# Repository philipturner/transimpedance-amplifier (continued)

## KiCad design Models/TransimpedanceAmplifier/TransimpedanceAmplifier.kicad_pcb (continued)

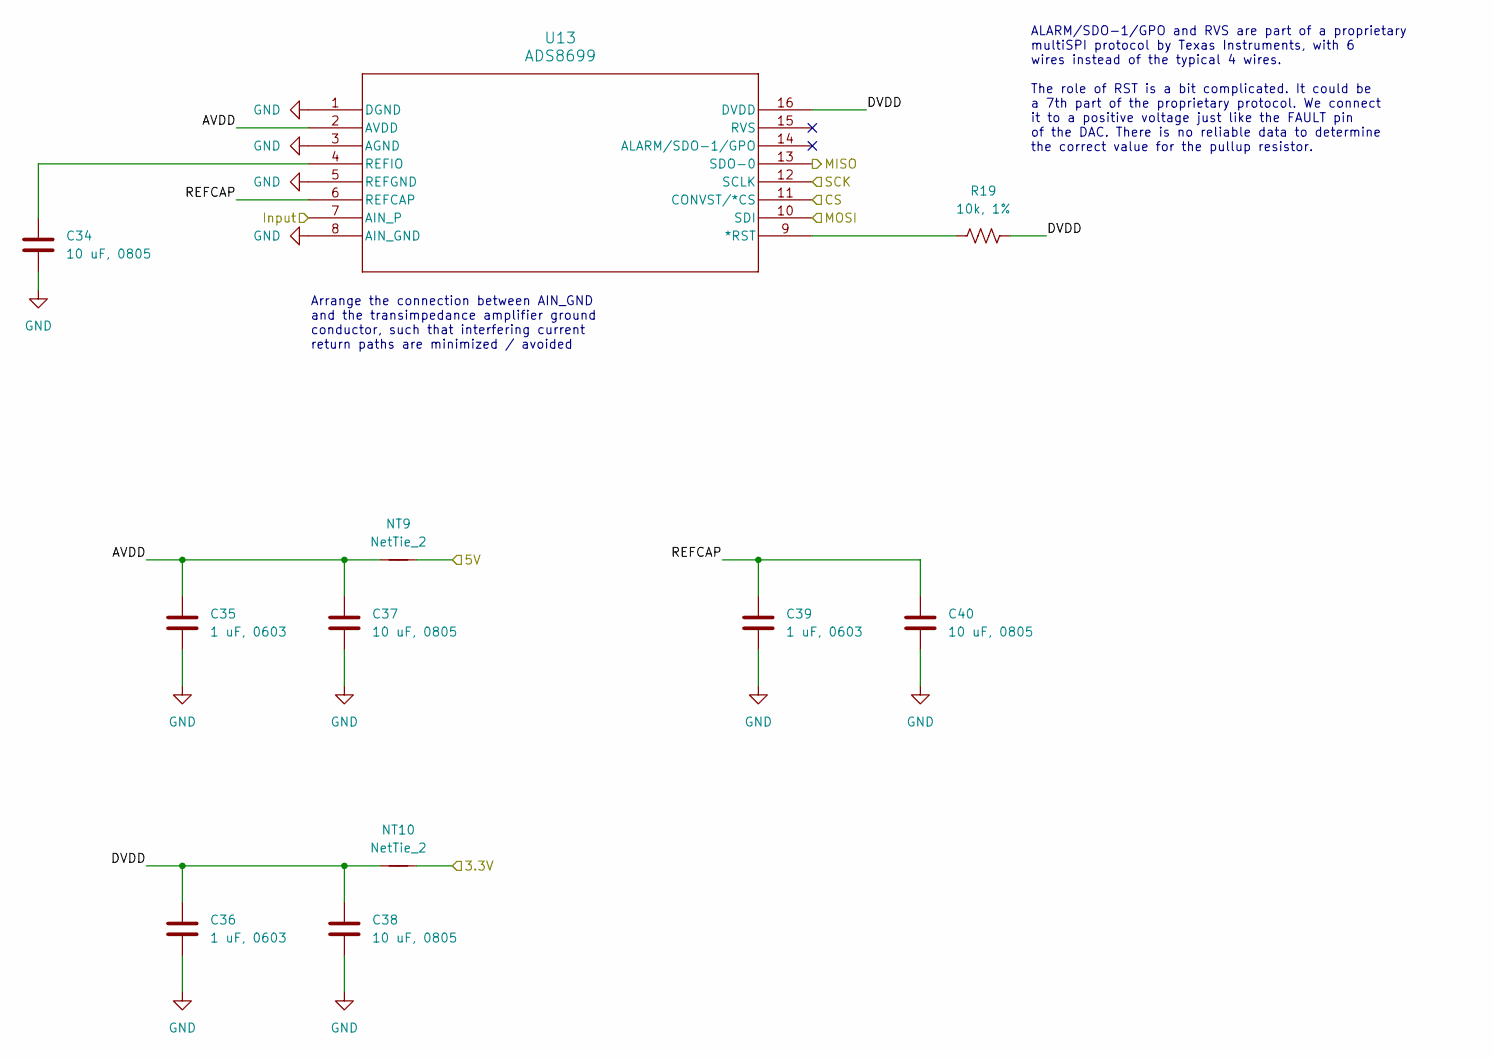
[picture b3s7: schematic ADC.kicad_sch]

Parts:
C34, C37, C38, C40: 10 uF, 0805; CAPC0805
C35, C36, C39: 1 uF, 0603; CAPC0603
NT9, NT10: NetTie_2; NetTie_0.2mm
R19: 10k, 1%; RESC0603
U13: ADS8699

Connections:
/3.3V_Converter: NT10.2; also elsewhere on the board
/5V_Converter: NT9.2; also elsewhere on the board
/CPU/ADC/AVDD: C35.1, C37.1, NT9.1, U13.2 (AVDD)
/CPU/ADC/CS: U13.11 (CONVST/*CS); also elsewhere on the board
/CPU/ADC/DVDD: C36.1, C38.1, NT10.1, R19.2, U13.16 (DVDD)
/CPU/ADC/MISO: U13.13 (SDO-0); also elsewhere on the board
/CPU/ADC/MOSI: U13.10 (SDI); also elsewhere on the board
/CPU/ADC/REFCAP: C39.1, C40.1, U13.6 (REFCAP)
/CPU/ADC/SCK: U13.12 (SCLK); also elsewhere on the board
/CPU/ADC_Input: U13.7 (AIN_P); also elsewhere on the board
GND: C34.2, C35.2, C36.2, C37.2, C38.2, C39.2, C40.2, U13.1 (DGND), U13.3 (AGND), U13.5 (REFGND), U13.8 (AIN_GND); also elsewhere on the board
unnamed: R19.1, U13.9 (*RST)
unnamed: C34.1, U13.4 (REFIO)

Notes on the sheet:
ALARM/SDO-1/GPO and RVS are part of a proprietary multiSPI protocol by Texas Instruments, with 6 wires instead of the typical 4 wires. The role of RST is a bit complicated. It could be a 7th part of the proprietary protocol. We connect it to a positive voltage just like the FAULT pin of the DAC. Th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
Arrange the connection between AIN_GND and the transimpedance amplifier ground conductor, such that interfering current return paths are minimized / avoided

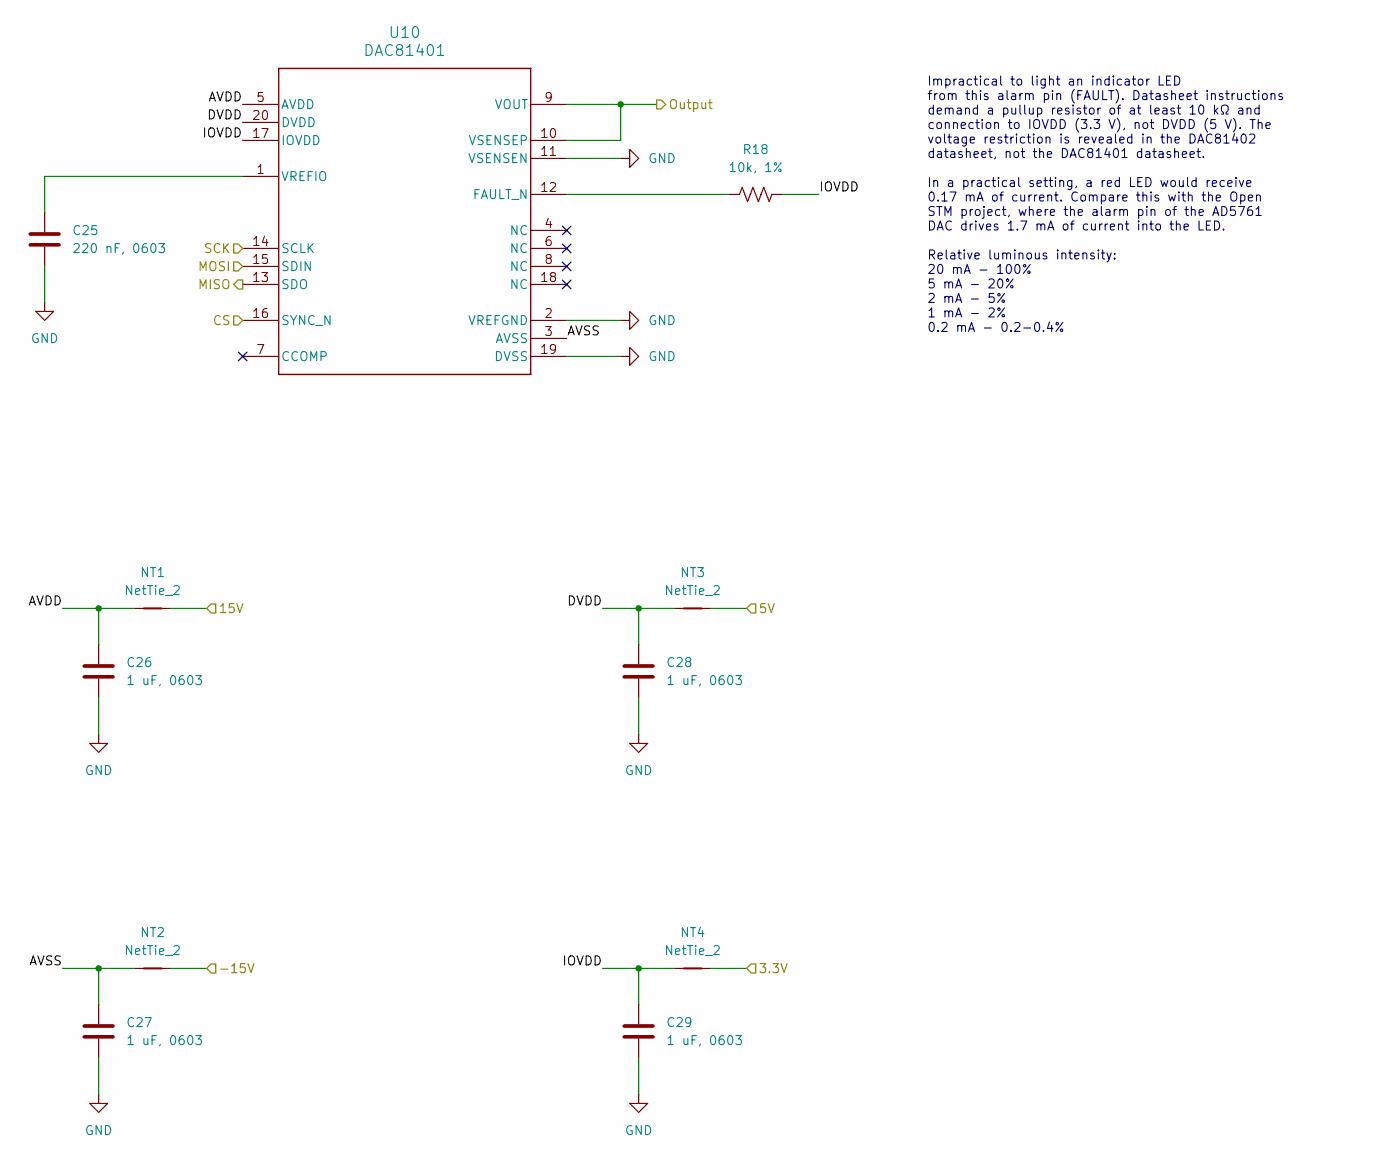
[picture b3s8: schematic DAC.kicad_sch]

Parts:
C25: 220 nF, 0603; CAPC0603
C26, C27, C28, C29: 1 uF, 0603; CAPC0603
NT1, NT2, NT3, NT4: NetTie_2; NetTie_0.2mm
R18: 10k, 1%; RESC0603
U10: DAC81401

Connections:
/3.3V_Converter: NT4.2; also elsewhere on the board
/5V_Converter: NT3.2; also elsewhere on the board
/15V: NT1.2; also elsewhere on the board
/-15V: NT2.2; also elsewhere on the board
/CPU/DAC/AVDD: C26.1, NT1.1, U10.5 (AVDD)
/CPU/DAC/AVSS: C27.1, NT2.1, U10.3 (AVSS)
/CPU/DAC/CS: U10.16 (SYNC_N); also elsewhere on the board
/CPU/DAC/DVDD: C28.1, NT3.1, U10.20 (DVDD)
/CPU/DAC/IOVDD: C29.1, NT4.1, R18.2, U10.17 (IOVDD)
/CPU/DAC/MISO: U10.13 (SDO); also elsewhere on the board
/CPU/DAC/MOSI: U10.15 (SDIN); also elsewhere on the board
/CPU/DAC/SCK: U10.14 (SCLK); also elsewhere on the board
/CPU/DAC_Output: U10.9 (VOUT), U10.10 (VSENSEP); also elsewhere on the board
GND: C25.2, C26.2, C27.2, C28.2, C29.2, U10.2 (VREFGND), U10.11 (VSENSEN), U10.19 (DVSS); also elsewhere on the board
unnamed: R18.1, U10.12 (FAULT_N)
unnamed: C25.1, U10.1 (VREFIO)

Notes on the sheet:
Impractical to light an indicator LED from this alarm pin (FAULT). Datasheet instructions demand a pullup resistor of at least 10 kΩ and connection to IOVDD (3.3 V), not DVDD (5 V). The voltage restriction is revealed in the DAC81402 datasheet, not the DAC81401 datasheet. In a practical setting, a 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

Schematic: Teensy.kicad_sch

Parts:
J11, J14: Conn_01x24_Socket; PinSocket_1x24
J12, J13: Conn_01x24_Pin
U14: Teensy4.1

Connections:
/CPU/Isolation/3.3V_Digital: J11.15, J14.22; also elsewhere on the board
/CPU/Isolation/CS_ADC_Digital: J14.5; also elsewhere on the board
/CPU/Isolation/CS_DAC_Digital: J14.4; also elsewhere on the board
/CPU/Isolation/GND_Digital: J11.1, J14.10, J14.23; also elsewhere on the board
/CPU/Isolation/MISO_Digital: J11.14; also elsewhere on the board
/CPU/Isolation/MOSI_Digital: J11.13; also elsewhere on the board
/CPU/Isolation/SCK_Digital: J14.11; also elsewhere on the board
unnamed: J12.1, U14.1 (GND)
unnamed: J12.2, U14.2 (0_RX1_CRX2_CS1)
unnamed: J12.3, U14.3 (1_TX1_CTX2_MISO1)
unnamed: J12.4, U14.4 (2_OUT2)
unnamed: J12.5, U14.5 (3_LRCLK2)
unnamed: J12.6, U14.6 (4_BCLK2)
unnamed: J12.7, U14.7 (5_IN2)
unnamed: J12.8, U14.8 (6_OUT1D)
unnamed: J12.9, U14.9 (7_RX2_OUT1A)
unnamed: J12.10, U14.10 (8_TX2_IN1)
unnamed: J12.11, U14.11 (9_OUT1C)
unnamed: J12.12, U14.12 (10_CS_MQSR)
unnamed: J12.13, U14.13 (11_MOSI_CTX1)
unnamed: J12.14, U14.14 (12_MISO_MQSL)
unnamed: J12.15, U14.15 (3V3)
unnamed: J12.16, U14.16 (24_A10_TX6_SCL2)
unnamed: J12.17, U14.17 (25_A11_RX6_SDA2)
unnamed: J12.18, U14.18 (26_A12_MOSI1)
unnamed: J12.19, U14.19 (27_A13_SCK1)
unnamed: J12.20, U14.20 (28_RX7)
unnamed: J12.21, U14.21 (29_TX7)
unnamed: J12.22, U14.22 (30_CRX3)
unnamed: J12.23, U14.23 (31_CTX3)
unnamed: J12.24, U14.24 (32_OUT1B)
unnamed: J13.1, U14.25 (33_MCLK2)
unnamed: J13.2, U14.26 (34_RX8)
unnamed: J13.3, U14.27 (35_TX8)
unnamed: J13.4, U14.28 (36_CS)
unnamed: J13.5, U14.29 (37_CS)
unnamed: J13.6, U14.30 (38_CS1_IN1)
unnamed: J13.7, U14.31 (39_MISO1_OUT1A)
unnamed: J13.8, U14.32 (40_A16)
unnamed: J13.9, U14.33 (41_A17)
unnamed: J13.10, U14.34 (GND)
unnamed: J13.11, U14.35 (13_SCK_LED)
unnamed: J13.12, U14.36 (14_A0_TX3_SPDIF_OUT)
unnamed: J13.13, U14.37 (15_A1_RX3_SPDIF_IN)
unnamed: J13.14, U14.38 (16_A2_RX4_SCL1)
unnamed: J13.15, U14.39 (17_A3_TX4_SDA1)
unnamed: J13.16, U14.40 (18_A4_SDA)
unnamed: J13.17, U14.41 (19_A5_SCL)
unnamed: J13.18, U14.42 (20_A6_TX5_LRCLK1)
unnamed: J13.19, U14.43 (21_A7_RX5_BCLK1)
unnamed: J13.20, U14.44 (22_A8_CTX1)
unnamed: J13.21, U14.45 (23_A9_CRX1_MCLK1)
unnamed: J13.22, U14.46 (3V3)
unnamed: J13.23, U14.47 (GND)
unnamed: J13.24, U14.48 (VIN)

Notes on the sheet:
Connected to low-cost Windows PC through Micro-USB port: 49 (VUSB) 66 (D-) 67 (D+) GND
All 3.3V pins are electrically equivalent. They connect to the same net in the Teensy 4.1 PCB schematic. In theory, I can draw 250 mA out of any one of them. Their physical separation is mostly an issue at high frequencies, where local decoupling networks are used anyway. The same should be true ab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

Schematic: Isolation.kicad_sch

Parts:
C30, C31, C32, C33: 100 nF, 0603; CAPC0603
NT5, NT6, NT7, NT8: NetTie_2; NetTie_0.2mm
U11, U12: ISO7641FM

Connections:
/3.3V_Converter: NT7.2, NT8.2, U11.10 (EN2), U12.10 (EN2); also elsewhere on the board
/CPU/ADC/CS: U12.13 (OUTB); also elsewhere on the board
/CPU/ADC/MISO: U12.11 (IND); also elsewhere on the board
/CPU/ADC/MOSI: U12.14 (OUTA); also elsewhere on the board
/CPU/ADC/SCK: U12.12 (OUTC); also elsewhere on the board
/CPU/DAC/CS: U11.14 (OUTA); also elsewhere on the board
/CPU/DAC/MISO: U11.11 (IND); also elsewhere on the board
/CPU/DAC/MOSI: U11.13 (OUTB); also elsewhere on the board
/CPU/DAC/SCK: U11.12 (OUTC); also elsewhere on the board
/CPU/Isolation/3.3V_Digital: NT5.1, NT6.1, U11.7 (EN1), U12.7 (EN1); also elsewhere on the board
/CPU/Isolation/CS_ADC_Digital: U12.4 (INB); also elsewhere on the board
/CPU/Isolation/CS_DAC_Digital: U11.3 (INA); also elsewhere on the board
/CPU/Isolation/GND_Digital: C30.2, C31.2, U11.2 (GND1), U11.8 (GND1), U12.2 (GND1), U12.8 (GND1); also elsewhere on the board
/CPU/Isolation/MISO_Digital: U11.6 (OUTD), U12.6 (OUTD); also elsewhere on the board
/CPU/Isolation/MOSI_Digital: U11.4 (INB), U12.3 (INA); also elsewhere on the board
/CPU/Isolation/SCK_Digital: U11.5 (INC), U12.5 (INC); also elsewhere on the board
/CPU/Isolation/VCC1_ADC: C31.1, NT6.2, U12.1 (VCC1)
/CPU/Isolation/VCC1_DAC: C30.1, NT5.2, U11.1 (VCC1)
/CPU/Isolation/VCC2_ADC: C33.1, NT8.1, U12.16 (VCC2)
/CPU/Isolation/VCC2_DAC: C32.1, NT7.1, U11.16 (VCC2)
GND: C32.2, C33.2, U11.9 (GND2), U11.15 (GND2), U12.9 (GND2), U12.15 (GND2); also elsewhere on the board

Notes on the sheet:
Analog / High Voltage
Specifications from table instead of graph: 0 Mbps rate condition: I_CC1 = 2.0-3.0 mA I_CC2 = 3.3-5.0 mA 25 Mbps rate condition: I_CC1 = 3.4-4.5 mA I_CC2 = 6.1-7.6 mA 50 Mbps rate condition (extrapolation): I_CC1 = 4.8-6.1 mA I_CC2 = 8.8-10.8 mA
Digital
Current demands for ISO7641FM @ 3.3 V 0 Mbps rate condition: I_CC1 = 2.0 mA I_CC2 = 3.6 mA 25 Mbps rate condition: I_CC1 = 3.6 mA I_CC2 = 6.0 mA 50 Mbps rate condition: I_CC1 = 4.8 mA I_CC2 = 8.8 mA

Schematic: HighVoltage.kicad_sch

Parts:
C17: 220 nF, 0603; CAPC0603
C18: 100 nF, 0603; CAPC0603
C19, C20: 1 uF, 0805; CAPC0805
D8, D9: D_Schottky; SOD-123
U6: LM7915, -15V, 5%; TO-220
U7: LM7815, 15V, 5%; TO-220

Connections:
/15V: C18.1, D8.1 (K), U7.3 (OUTPUT); also elsewhere on the board
/-15V: C19.2, D9.2 (A), U6.3 (OUT); also elsewhere on the board
/Power/Batteries/27V: C17.1, U7.1 (INPUT); also elsewhere on the board
/Power/Batteries/-27V: C20.1, U6.2 (IN); also elsewhere on the board
GND: C17.2, C18.2, C19.1, C20.2, D8.2 (A), D9.1 (K), U6.1 (GND), U7.2 (GND); also elsewhere on the board

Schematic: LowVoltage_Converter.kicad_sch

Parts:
C21: 220 nF, 0603; CAPC0603
C22, C24: 1 uF, 0805; CAPC0805
C23: 100 nF, 0603; CAPC0603
D10, D11: D_Schottky; SOD-123
U8: LM7805, 5V, 5%; TO-220
U9: TLV76133, 3.3V, 1%; SOT-223

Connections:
/3.3V_Converter: C24.1, D11.1 (K), U9.4 (OUT); also elsewhere on the board
/5V_Converter: C22.1, C23.1, D10.1 (K), U8.3 (OUTPUT), U9.3 (IN); also elsewhere on the board
/Power/Batteries/18V: C21.1, U8.1 (INPUT); also elsewhere on the board
GND: C21.2, C22.2, C23.2, C24.2, D10.2 (A), D11.2 (A), U8.2 (GND), U9.1 (GND); also elsewhere on the board

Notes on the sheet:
Dropout voltage: 0.9 V (typical), 1.6 V (max) Variation with load: 0.9 V (1.0 A) 0.7 V (0.8 A) 0.2 V (0.1 A) Dropout voltage exceeds expected value when Vout + 1.5 V < 4.0 V

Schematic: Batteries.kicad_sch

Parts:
BT1, BT2: BatteryModule

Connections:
/Power/Batteries/18V: BT1.5 (BT3(+)); also elsewhere on the board
/Power/Batteries/27V: BT1.1 (BT1(+)); also elsewhere on the board
/Power/Batteries/-27V: BT2.4 (BT2(-)); also elsewhere on the board
GND: BT1.8 (BT4(-)), BT2.5 (BT3(+)), BT2.8 (BT4(-)); also elsewhere on the board
unnamed: BT1.2 (BT1(-)), BT1.3 (BT2(+))
unnamed: BT1.4 (BT2(-)), BT2.7 (BT4(+))
unnamed: BT1.6 (BT3(-)), BT1.7 (BT4(+))
unnamed: BT2.1 (BT1(+)), BT2.6 (BT3(-))
unnamed: BT2.2 (BT1(-)), BT2.3 (BT2(+))

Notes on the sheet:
Positive power supply Guaranteed above 17.5 V for 0.3 A-hours Theoretical upper bound: 28.6 V 20 mA load condition ~26.9 V @ 0.0 hours ~17.5 V @ 15.0 hours 100 mA load condition ~26.6 V @ 0.0 hours ~17.5 V @ 3.0 hours
Logic power supply Guaranteed above 7.5 V for 0.3 A-hours Theoretical upper bound: 19.1 V 20 mA load condition ~17.9 V @ 0.0 hours ~7.5 V @ 15.0 hours 100 mA load condition ~17.7 V @ 0.0 hours ~7.5 V @ 3.0 hours
Power / Thermal Concerns Internal resistance: 1-2 Ω per battery Maximum current load: 50 mA I2R power dissipation: 5 mW per battery
6 hour lifetime easily exceeded during a long debugging session; order a spare 8-pack of 9 V batteries
Negative power supply Guaranteed below -17.5 V for 0.3 A-hours

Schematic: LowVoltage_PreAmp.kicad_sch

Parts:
C1: 220 nF, 0603; CAPC0603
C2: 100 nF, 0603; CAPC0603
C3, C4: 1 uF, 0805; CAPC0805
D1, D2: D_Schottky; SOD-123
U1: LM7905, -5V, 5%; TO-220
U2: LM7805, 5V, 5%; TO-220

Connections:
/5V_PreAmp: C2.1, D1.1 (K), U2.3 (OUTPUT); also elsewhere on the board
/15V: C1.1, U2.1 (INPUT); also elsewhere on the board
/-5V_PreAmp: C3.2, D2.2 (A), U1.3 (OUT); also elsewhere on the board
/-15V: C4.1, U1.2 (IN); also elsewhere on the board
GND: C1.2, C2.2, C3.1, C4.2, D1.2 (A), D2.1 (K), U1.1 (GND), U2.2 (GND); also elsewhere on the board

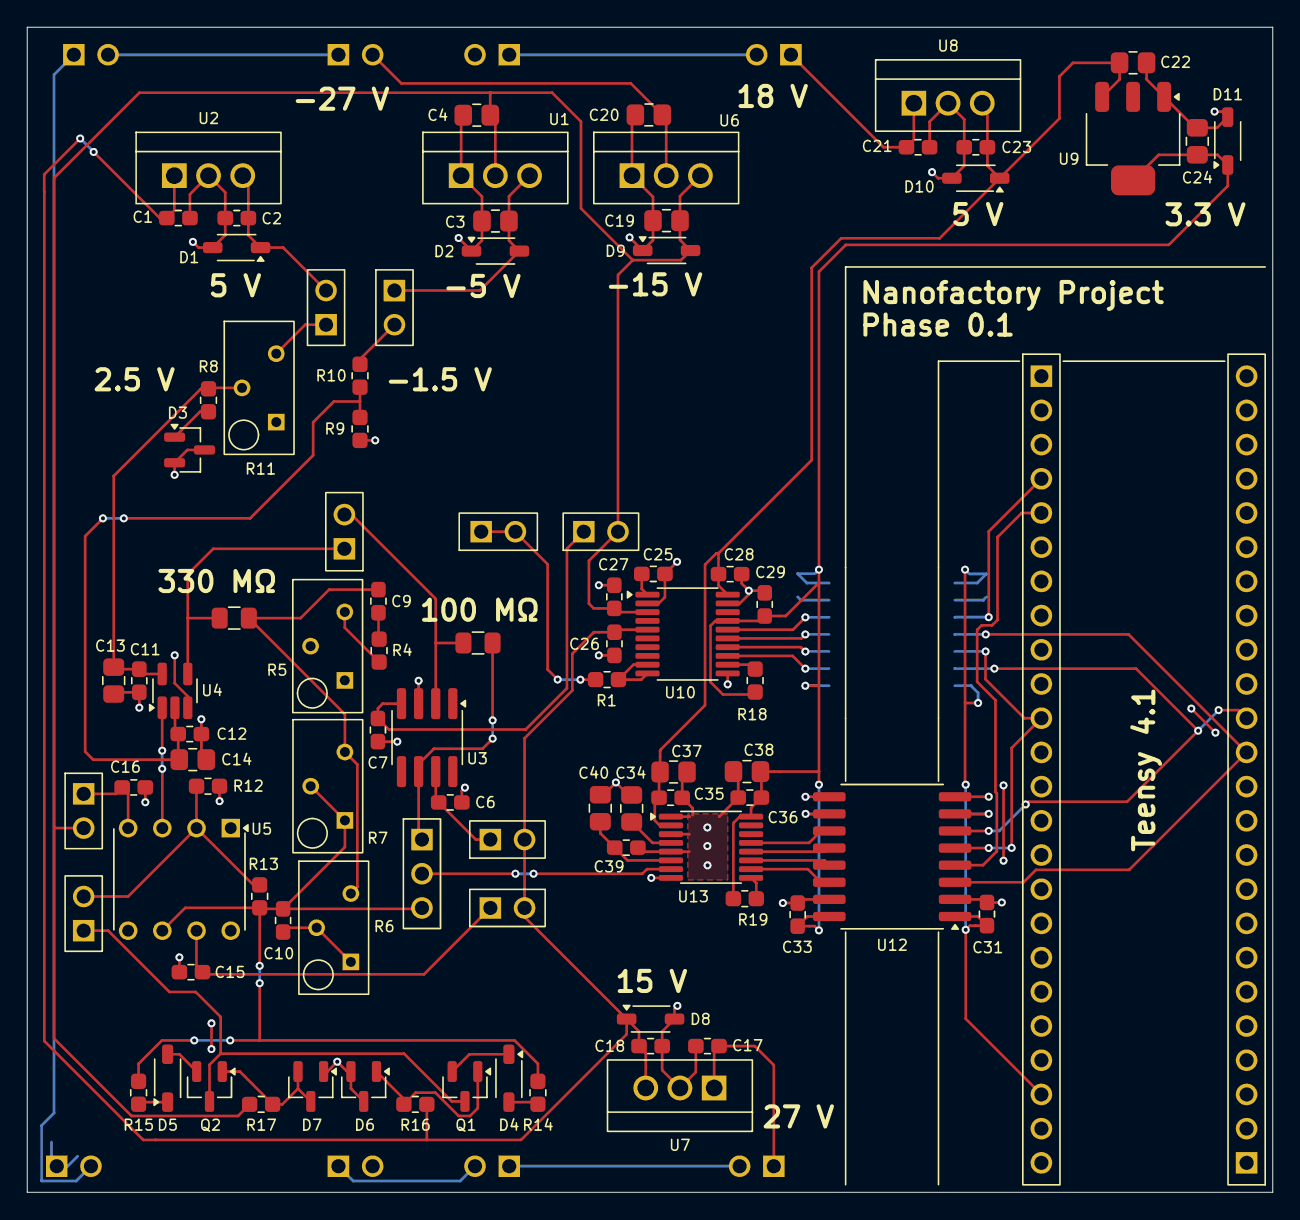
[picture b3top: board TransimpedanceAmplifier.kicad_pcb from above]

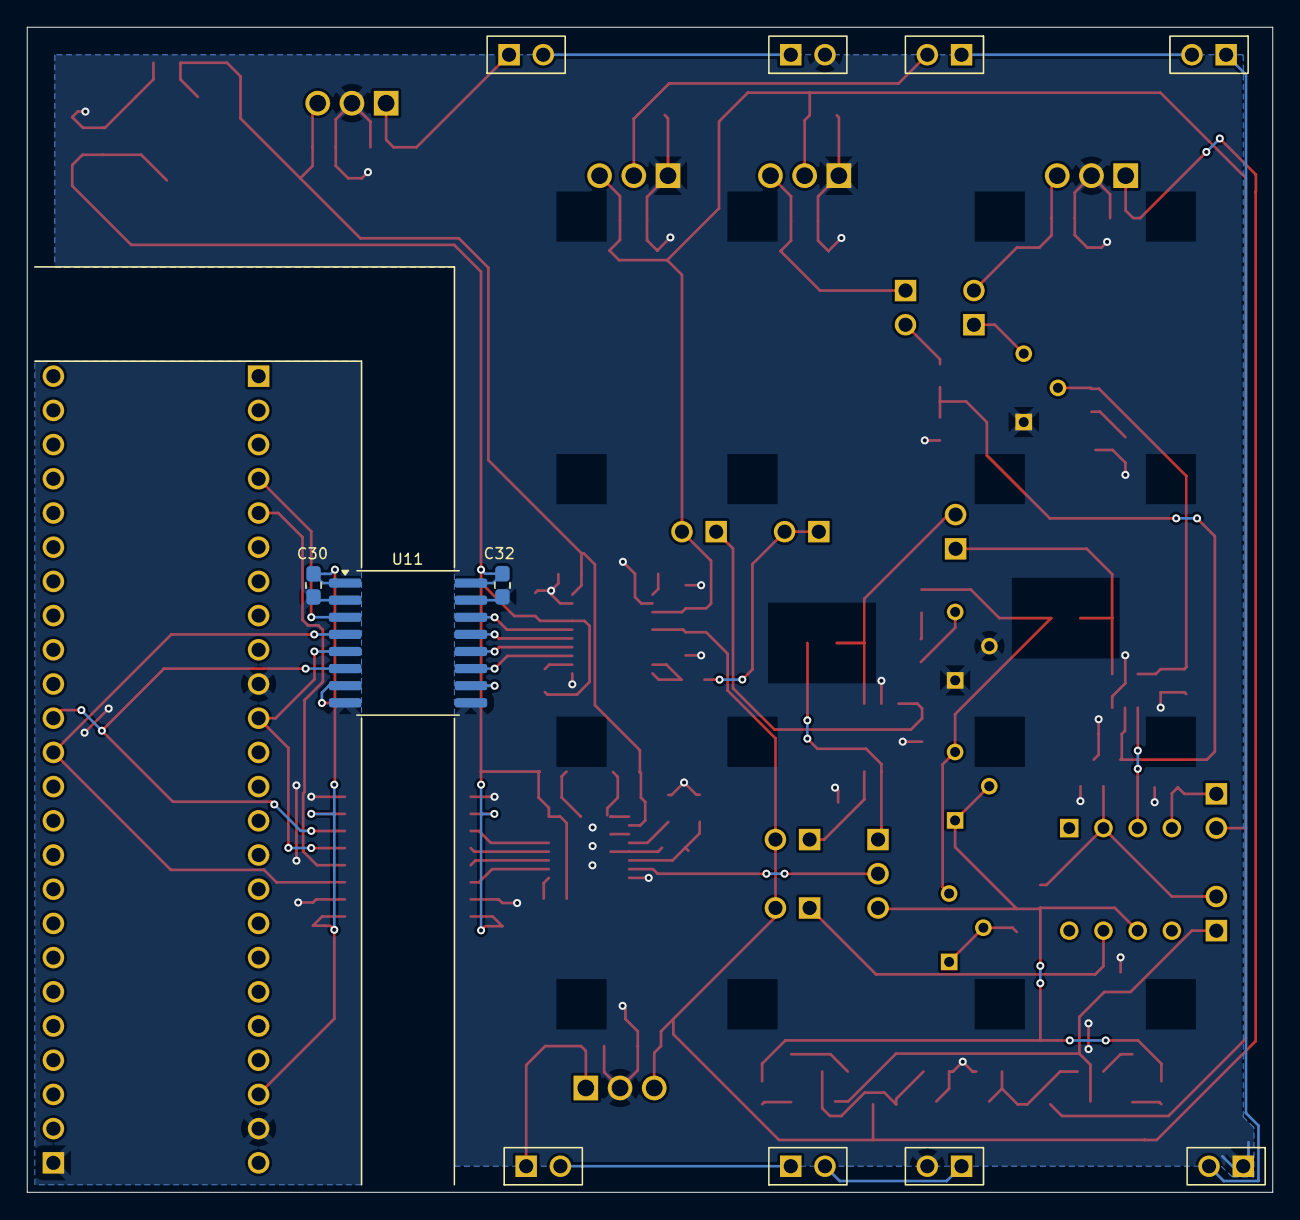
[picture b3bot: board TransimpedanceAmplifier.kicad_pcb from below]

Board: 2 copper layers, 92.5 x 86.5 mm, 107 parts (7 on the bottom side), 74 nets.

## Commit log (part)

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2025-08-28 Save progress
2025-08-28 Patched the incorrect decoupling network for the isolators
2025-08-28 Resolved some ERC errors by removing the check on pin type compatibility
2025-08-28 Set all analog pins of the Teensy as not connected
2025-08-28 Set Teensy digital pins 0-10 as not connected
2025-08-28 Set all the remaining pins as not connected
2025-08-28 Bringing out symbol descriptions as preparation for proper annotation
2025-08-28 Overhauled all of the annotations
2025-08-28 Made a net tie footprint
2025-08-28 Every decoupling network now has a dedicated net label
2025-08-28 Reorganized the DAC decoupling network for ease of modification
2025-08-28 First successful ERC
2025-08-29 Got all the files properly set up now
2025-08-29 Setting up the battery module PCB
2025-08-29 Aligned the text artwork for one battery, three left to go
2025-08-29 Finished the PCB for the battery holder
2025-08-29 Placed first two keepout zones of the footprint
2025-08-29 Placed all keepout zones correctly
2025-08-29 Almost finished with the battery footprint
2025-08-29 Finished battery module symbol
2025-08-29 Completely fixed the batteries
2025-08-29 Resolved input overvoltage protection for AD8615 and DAC
2025-08-29 Finalized the last detail of the schematic
2025-08-29 Working on filling in the last details of the schematics
2025-08-29 Fixed a bug in footprint assignment
2025-08-30 Added important links regarding high-voltage electronics
2025-08-30 Almost done with generating bill of materials
2025-08-30 Going to shift all the expensive, hard-to-find ICs over to Mouser
2025-08-30 Starting major changes in response to the SOIC-8 version of OP37 being out of stock
2025-08-30 Patching up the bill of materials now
2025-08-30 Exclude these pin headers from the BOM; they are just cheap breakaway pins
2025-08-30 Typo fix
2025-08-30 Finished the PDIP-8 footprint
2025-08-30 Shifted the reference designator closer to the footprint, making it easier to use during PCB layout
2025-08-30 Assigned the last footprint
2025-08-30 Some initial steps toward a first draft of layout
2025-08-30 Experimenting with the Texas Instruments recommended decoupling network for the DAC
2025-08-30 Arranged the capacitors in the decoupling network quite tightly around the IC
2025-08-30 Revised connectivity to improve physical layout
2025-08-30 Finished the DAC decoupling network
2025-08-30 Beginning to arrange the components of the ADC
2025-08-30 Removed some complexity from the schematic while solving the layout problem
2025-08-30 Finished the ADC footprint
2025-08-30 Solved a topology issue in a simpler way by flipping a chip to the other side of the board
2025-08-31 Patched the pin ordering of the isolators
2025-08-31 Finished the isolator decoupling networks
2025-08-31 Attempt to make a Git commit
2025-08-31 Finished the draft of the TLV761 decoupling network
2025-08-31 Finalized a few variables in the OPA828 subsystem
2025-08-31 Improvements to the ADS8699 decoupling network
2025-08-31 Keeping the PreAmp voltage divider unresolved for now
2025-08-31 More refinement regarding current return paths in the ADS8699 decoupling network
2025-08-31 Resolved some of the OP37's auxiliary components
2025-08-31 Sorting out the high-level arrangement of subsystems
2025-08-31 Now at approximately 17 in^2 of board size
2025-08-31 15 in^2 at this point, sufficient to finalize the general power topology
2025-08-31 Added notes for power wiring
2025-09-01 Polarized the battery module by offsetting one of the pin headers
2025-09-01 Rewired the battery modules
2025-09-01 Some more tweaks to prepare for the next round of work on the PCB
2025-09-01 Addressed the routing of this troublesome signal trace
2025-09-01 Carefully arranged the pole-zero compensation network to minimize board area
2025-09-01 Removed the J designator from 2-3 terminal pin sockets
2025-09-01 Solved some problems with routing the OPA828 power pins
2025-09-01 Resolved the unknown about best wiring of trimpots for the pole-zero compensation network
2025-09-01 Marked all finalized component positions
2025-09-01 Now we're at 13 in^2
2025-09-01 First walkthrough of wiring together this network
2025-09-01 Let's hope this setup works
2025-09-01 Wired that up, looks good
2025-09-01 Used 2.54 mm grid paradigm to position these jumper headers
2025-09-01 Finalized a few more details
2025-09-01 Finalized the positions of all expensive chips and their nearby components
2025-09-01 Positions of the battery modules are now locked
2025-09-01 Started routing a few of the 15 V power traces
2025-09-01 Resolved another round of unknowns
2025-09-01 Aligned the voltage regulators
2025-09-01 Next step is silkscreen labels for the voltages
2025-09-01 Finalized all of the text labels
2025-09-01 Very good developments. Next step is the voltage divider.
2025-09-01 Connected an important power trace
2025-09-01 Rewired the -15 V power trace
2025-09-01 Locked the recently modified components
2025-09-01 Fixed a bug in the schematic: the -1.5 V net was not connected to its voltage divider
2025-09-01 That should be all major traces wired up, except for the Teensy side
2025-09-01 Locked the positions of the Teensy pin headers
2025-09-01 Incorporated an improved battery module footprint
2025-09-01 Got the Edge.Cuts, now just need to draw the isolation barrier
2025-09-01 Showing the true isolation barrier on the silkscreen. A slow but steady process.
2025-09-01 Ready to wire up the Teensy wires and then do the ground planes
2025-09-02 Avoid using this 3.3V_Digital pin, it's a major pain
2025-09-02 All of the pins should be connected now
2025-09-02 Fixed all DRC violations
2025-09-02 Commit project
2025-09-02 Fixed that annoying edge of the high-voltage ground plane
2025-09-04 Added a KiCad project for the practice board
2025-09-04 Elaborated more on the board
2025-09-04 Going to practice laying out the resistors near a chip, although the annotations will likely be overwritten later, requiring a duplication of the work for PCB layout
2025-09-04 Rough sketch of the layout resulted in a calculated price of
2025-09-04 Finally settled on the relative layout of all parts on the board
2025-09-05 Finished the schematic for the practice board
2025-09-05 Aligned the U1 and U2 subsystems
2025-09-05 Fixed some of the silkscreen for the battery module
2025-09-05 Wired everything up, but next step is to connect half of the THT and 0805 to a ground plane
2025-09-05 Finished the layout of the practice board
2025-09-08 Update the image with final costs
2025-09-08 Setting TODOs
2025-09-08 Update TODO
2025-09-08 Upload screenshots of confirmation emails
2025-09-08 Upload the OSH Park invoice screenshots
2025-09-08 Uploaded the Amazon invoice
2025-09-08 Upload the screenshot PNG files
2025-09-08 Test
2025-09-08 Put all images on the README
2025-09-09 A step toward setting up the simulation
2025-09-09 Figuring out the material properties for the simulation
2025-09-09 Uploaded in-progress simulation model
2025-09-10 First FEM simulation results
2025-09-10 These frequencies look like very good news
2025-09-10 Upload improved model
2025-09-12 Upload the first half of the images
2025-09-12 Upload the second half of the images
2025-09-12 Document the images on the README
2025-09-12 Upload image
2025-09-12 Add the first YouTube link of today
2025-09-16 First half of uploads
2025-09-16 Second half of uploads
2025-09-16 Upload journal entry
2025-09-17 Synchronize with main repo
2025-09-19 Starting the journal entry
2025-09-19 Add image
2025-09-20 Upload source code for failed test
2025-09-20 Upload code
2025-09-20 Still no luck, but at least the DAC didn't break
2025-09-20 Upload media
2025-09-21 Sync changes with KiCad prl
2025-09-21 Add entry to table of contents
2025-09-21 ADC finally works
2025-09-21 Got the time constant for when the shutdown happens
2025-09-21 Minimal reproducer for the Teensy bug has been identified
2025-09-21 Add first iteration of the design for this kHz loop test
2025-09-21 Upload results of timing fidelity test at 10 kHz
2025-09-21 Results of the timing fidelity test at 100 kHz
2025-09-21 Have not yet uploaded test 4
2025-09-22 Discovery
2025-09-22 Save progress on testing program
2025-09-22 Ready to start the test
2025-09-22 Massive bug fix, the DAC was not responding
2025-09-22 Upload the new test code, with only the ADC being tested
2025-09-22 Fixed the bug by just going to a slower clock speed
2025-09-22 Upload results of latest test
2025-09-22 Typo fix, this is a THT package
2025-09-23 Patched the SPICE simulation model from the home-built-stm repo
2025-09-23 Ran some frequency response tests, will upload results in next commit
2025-09-23 Working on the journal entry
2025-09-23 Test the look of one image
2025-09-23 Added the other graphs
2025-09-23 May have found a culprit
2025-09-23 Identified a probable cause of the problem
2025-09-23 Results of calibration
2025-09-23 Preparing the tests
2025-09-23 Check how the formatting looks
2025-09-23 Results of some tests
2025-09-23 Results of the second test
2025-09-23 Check whether this even bolds in the table
2025-09-23 Highlighted where resistor values are changed
2025-09-23 Conclusion of today's journal entry
2025-09-23 Typo fixes
2025-09-24 Fill in some of the measurements
2025-09-24 Formatting fix
2025-09-24 Prepared the data collection
2025-09-24 Strange multimeter readings for V- Low
2025-09-24 Upload some more measurements
2025-09-24 Added images of the newly installed AD8615
2025-09-24 Finished tuning the compensation network
2025-09-24 Recalibration after strange effect of turning on OP2
2025-09-25 Add video link
2025-09-25 Upload the image for the journal entry
2025-10-26 Add lowpass filter simulation
2025-10-26 Upload images
2025-10-26 Link the media to the README
2025-10-27 This symbol is unworkable
2025-10-27 Added the datasheets
2025-10-27 Made custom symbol, much cleaner
2025-10-27 Need to migrate this to a hierarchical sheet
2025-10-27 Sorting into hierarchical sheets
2025-10-29 Deleting the lock file?
2025-10-30 Filled in breadboard schematic, now need purchase links
2025-10-30 Did the BOM
2025-11-03 Fix the orientation
2025-11-03 Fix the schematic
2025-11-03 Upload the image
2025-11-03 Return to this later
2025-11-03 Fixed the annotation
2025-11-04 Upload progress on Oscilloscope1
2025-11-05 Found a way
2025-11-05 Memory successfully allocated
2025-11-05 Need another mode with even greater zoom
2025-11-05 Fix the formatting
2025-11-05 Fixed a bug
2025-11-06 Corrected the sign of the currents
2025-11-06 Added voltage divider to schematic
2025-11-06 Exclude this from the BOM
2025-11-06 Specified the tests to run
2025-11-06 Better wording
2025-11-06 Some data
2025-11-06 Save data
2025-11-06 See how this looks
2025-11-06 Check how this looks
2025-11-07 See what the tables look like
2025-11-07 Labels for the changes
2025-11-07 Start video script
2025-11-07 This change did not commit
2025-11-08 BIG IMPORTANT WORDS I WANT TO SHOW OFF TO VIEWERS
